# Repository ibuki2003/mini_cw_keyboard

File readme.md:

# モールスキーボード

## 使い方

モールス信号でPCに文字を入力することができる、小型のキーボードです。
お使いのPCのUSB端子に接続し、タッチパッド（銀色の部分）を使ってモールス信号を入力すると、対応するキーが入力されます。

## GitHubリポジトリについて

### board

回路図、基板レイアウトがKiCAD形式で置かれています。
KiCADはオープンソースソフトウェアであり、Windows, Mac, Linux版等が入手可能です。

### program

マイコンに書き込んだプログラムのソースコードが置かれています。

## License

The program depends on the following libraries:

- V-USB
    - https://www.obdev.at/vusb/

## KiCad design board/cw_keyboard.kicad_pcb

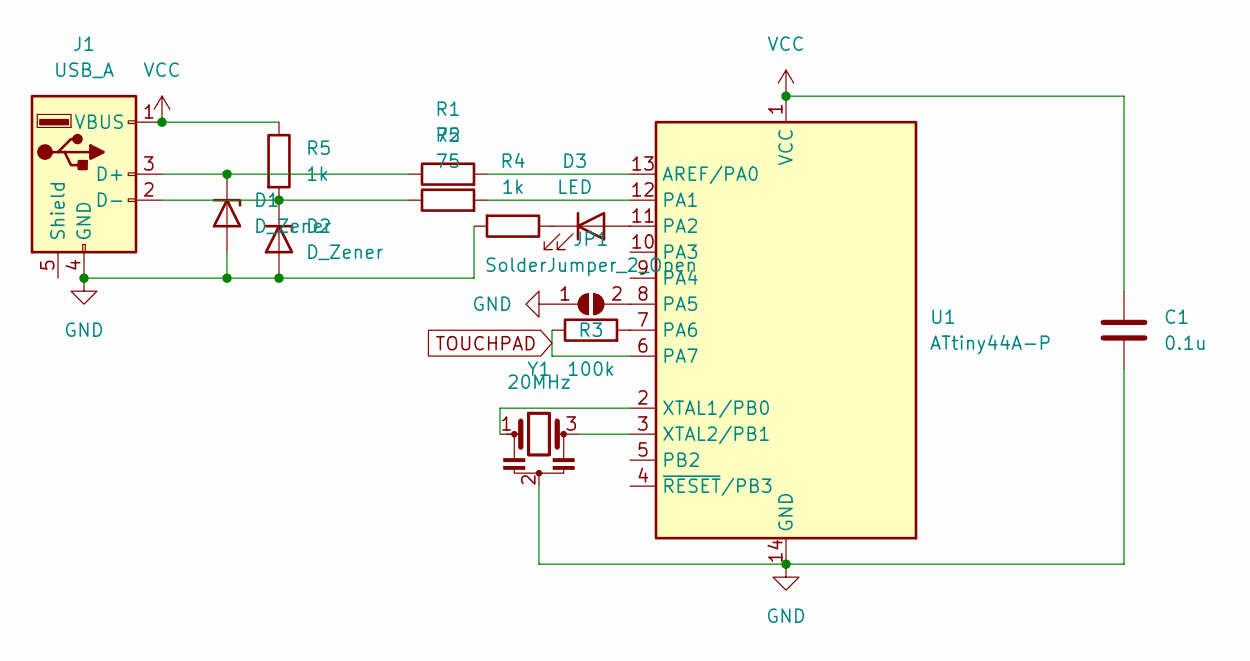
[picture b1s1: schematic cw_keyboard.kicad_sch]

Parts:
C1: 0.1u; C_0603_1608Metric_Pad1.08x0.95mm_HandSolder
D1, D2: D_Zener; D_UMD2
D3: LED; LED_0603_1608Metric_Pad1.05x0.95mm_HandSolder
J1: USB_A; USB-A_Connector_Direct
JP1: SolderJumper_2_Open; SolderJumper-2_P1.3mm_Open_RoundedPad1.0x1.5mm
R1, R2: 75; R_0603_1608Metric_Pad0.98x0.95mm_HandSolder
R3: 100k; R_0603_1608Metric_Pad0.98x0.95mm_HandSolder
R4, R5: 1k; R_0603_1608Metric_Pad0.98x0.95mm_HandSolder
U1: ATtiny44A-P; DIP-14_W7.62mm
Y1: 20MHz; PinHeader_1x03_P2.54mm_Vertical

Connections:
GND: C1.2, D1.2 (A), D2.2 (A), J1.4 (GND), JP1.1 (A), R4.2, U1.14 (GND), Y1.2
unnamed: D1.1 (K), J1.3 (D+), R1.1
unnamed: D2.1 (K), J1.2 (D-), R2.1, R5.2
unnamed: D3.2 (A), U1.11 (PA2)
unnamed: D3.1 (K), R4.1
unnamed: JP1.2 (B), U1.8 (PA5)
unnamed: R1.2, U1.13 (AREF/PA0)
unnamed: R2.2, U1.12 (PA1)
unnamed: R3.2, U1.7 (PA6)
unnamed: U1.2 (XTAL1/PB0), Y1.1
unnamed: U1.3 (XTAL2/PB1), Y1.3
TOUCHPAD: R3.1, U1.6 (PA7)
VCC: C1.1, J1.1 (VBUS), R5.1, U1.1 (VCC)

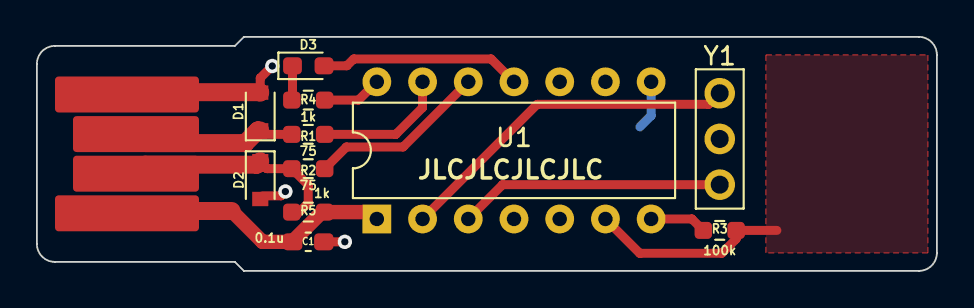
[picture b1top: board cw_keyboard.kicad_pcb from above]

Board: 2 copper layers, 50.0 x 13.0 mm, 13 parts (1 on the bottom side), 13 nets.

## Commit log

2023-10-21 build: add v-usb as submodule
2023-10-21 feat: it works
2023-10-26 build: change chip model to tiny44A
2023-10-26 feat: time dependent input
2023-10-26 feat: implement touch sensor
2023-10-28 feat: morse decoding
2023-10-28 feat: add pcb design files
2023-10-28 feat: shift key
2023-11-02 fix: submodule location
2023-11-07 fix: correct pin number
2023-11-07 feat: add bypass capacitor
2023-11-07 chore: ignore out file
2023-11-07 feat: add layout-specific symbols
2023-11-08 feat: add jumper to switch US/JIS layout
2023-11-08 fix: twist pair distance
2023-11-19 build: add phony tasks
2023-11-19 feat: switch key layout dynamically
2023-11-20 fix: fusebit comment was wrong
2023-11-22 feat: update tresholds
2023-11-25 fix: update keycode for jis layout
2023-12-05 docs: update documentations
